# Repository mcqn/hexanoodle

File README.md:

# hexanoodle
A CH32V203 microcontroller board for driving six LED noodles

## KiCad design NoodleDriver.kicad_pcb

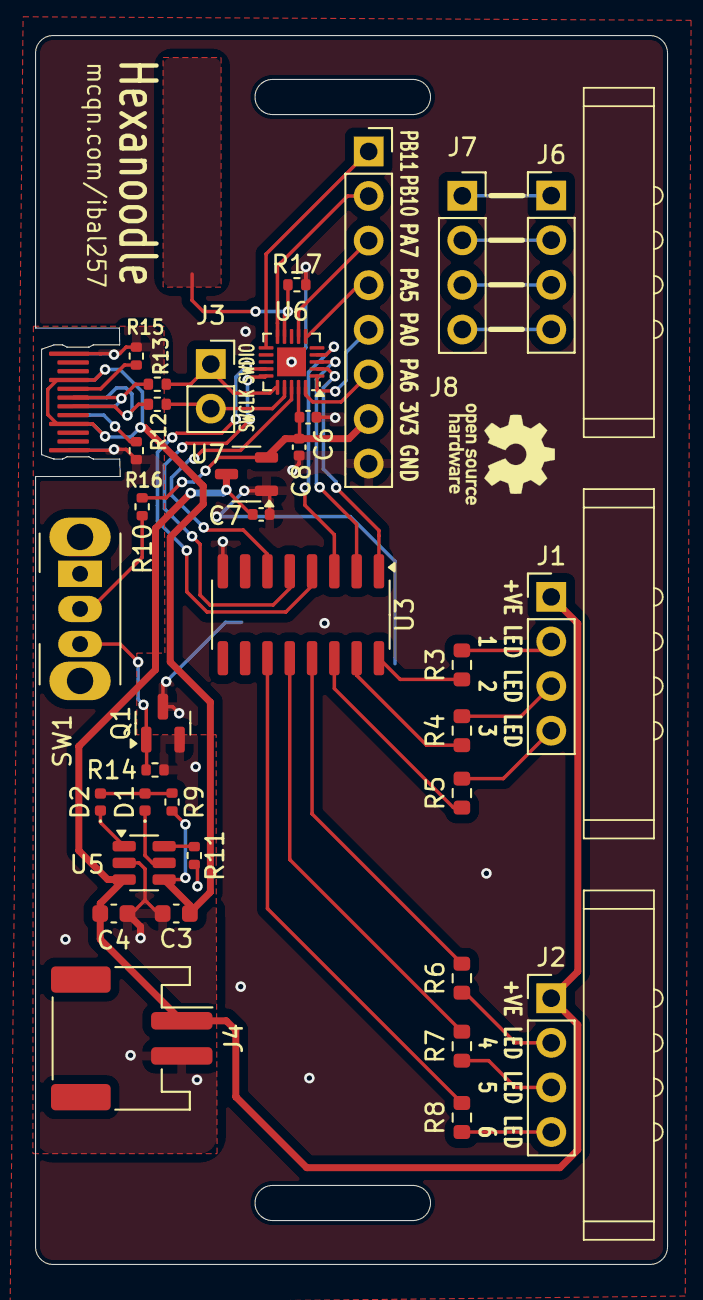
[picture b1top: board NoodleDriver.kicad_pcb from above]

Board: 2 copper layers, 36.0 x 70.0 mm, 36 parts (0 on the bottom side), 46 nets.

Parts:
C3, C4: 10uF; C_0603_1608Metric
C6: 0.1uF; C_0402_1005Metric
C7, C8: 1uF; C_0402_1005Metric
D1, D2: LED; LED_0402_1005Metric
J1, J2, J6: Conn_01x04; MagneticPogoPinConnector_1x04_P2.54mm_Horizontal
J3: Conn_01x02; PinSocket_1x02_P2.54mm_Vertical
J4: Conn_01x02_Socket; JST_PH_S2B-PH-SM4-TB_1x02-1MP_P2.00mm_Horizontal
J5: USB_C_Receptacle_USB2.0_16P; USB_C_PADDLE
J7: Conn_01x04; PinSocket_1x04_P2.54mm_Vertical
J8: Conn_01x08; PinSocket_1x08_P2.54mm_Vertical
Q1: JSM2302; SOT-23
R3, R4, R5, R6, R7, R8: 33R; R_0603_1608Metric
R9: 560R; R_0402_1005Metric
R10: 10K; R_0402_1005Metric
R11: 2K; R_0402_1005Metric
R12, R13: 22R; R_0402_1005Metric
R14: 100K; R_0402_1005Metric
R15, R16: 5K1; R_0402_1005Metric
R17: 1M; R_0402_1005Metric
SW1: On/Off; SW_Slide_SPDT_Angled_CK_OS102011MA1Q
U3: ULN2001; SOIC-16_3.9x9.9mm_P1.27mm
U5: TP4057; TSOT-23-6
U6: CH32V203F8U6; QFN-20-1EP_3x3mm_P0.4mm_EP1.65x1.65mm
U7: DS8242-33S3; SOT-23-3

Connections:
+3V3: C6.1, C8.1, J8.7, R10.1, U6.19 (VDD), U7.2 (VO)
+BATT: C4.1, C7.1, J1.1, J2.1, J4.1, U5.3 (BAT), U7.3 (VI)
-BATT: C3.2, C4.2, J4.2, J5.A1 (GND), J5.A12 (GND), J5.B1 (GND), J5.B12 (GND), Q1.2 (S), R11.2, R14.2, R15.2, R16.2, U5.2 (GND)
GND: C6.2, C7.2, C8.2, J8.8, Q1.3 (D), R17.2, U3.8 (GND), U6.21 (GND), U7.1 (GND)
unnamed: D1.2 (A), D2.2 (A), R9.2
unnamed: D1.1 (K), U5.5 (STDBY)
unnamed: D2.1 (K), U5.1 (~CHRG)
unnamed: J1.2, R3.2
unnamed: J1.3, R4.2
unnamed: J1.4, R5.2
unnamed: J2.2, R6.2
unnamed: J2.3, R7.2
unnamed: J2.4, R8.2
unnamed: J5.A5 (CC1), R15.1
unnamed: J5.B5 (CC2), R16.1
unnamed: J5.A6 (D+), J5.B6 (D+), R13.2
unnamed: J5.A7 (D-), J5.B7 (D-), R12.1
unnamed: J6.1, J7.1
unnamed: J6.2, J7.2
unnamed: J6.3, J7.3
unnamed: J6.4, J7.4
unnamed: Q1.1 (G), R14.1, SW1.3 (C)
unnamed: R10.2, SW1.2 (B)
unnamed: R3.1, U3.16 (O1)
unnamed: R4.1, U3.15 (O2)
unnamed: R5.1, U3.14 (O3)
unnamed: R6.1, U3.13 (O4)
unnamed: R7.1, U3.12 (O5)
unnamed: R8.1, U3.11 (O6)
unnamed: R11.1, U5.6 (PROG)
PA0: J8.5, U6.1 (PA0)
PA1: U3.1 (I1), U6.2 (PA1)
PA2: U3.2 (I2), U6.3 (PA2)
PA3: U3.3 (I3), U6.4 (PA3)
PA5: J8.4, U6.6 (PA5)
PA6: J8.6, U6.20 (PA6)
PA7: J8.3, U6.7 (PA7)
PA8: U3.4 (I4), U6.14 (PA8)
PA9: U3.5 (I5), U6.15 (PA9)
PA10: U3.6 (I6), U6.18 (PA10)
PB1: R17.1, U6.9 (PB1)
PB10: J8.2, U6.10 (PB10)
PB11: J8.1, U6.11 (PB11)
SWCLK: J3.2, R12.2, U6.17 (SWCLK)
SWDIO: J3.1, R13.1, U6.16 (SWDIO)
VBUS: C3.1, J5.A4 (VBUS), J5.A9 (VBUS), J5.B4 (VBUS), J5.B9 (VBUS), R9.1, U5.4 (V_{CC})

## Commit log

2025-08-21 First sketch of design using WS2811 drivers to drive more noodles. Part of #8
2025-09-17 Add a microcontroller, and regulator and USB-C connector. Checkin before I try swapping out the microbit and 0.1" headers. Part of #8
2025-09-24 Exclude the USB contacts from the solderpaste layers.
2025-10-05 Final tuning of prototype board, which we've ordered a handful of prototypes to be fabbed. Part of #8
2025-10-06 Add licence. OSHW FTW!
2025-11-12 Fix footprint bugs (and remove WS2811 interfaces). Part of #5
